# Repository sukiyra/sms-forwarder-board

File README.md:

# SMS Forwarder Board

面向 ESP32-C3 与 ML307 系列蜂窝模组的短信网关固件、Web 管理台和 Windows 批量量产工具。

这是由 [sukiyra](https://github.com/sukiyra) 独立维护和发布的工程仓库，GitHub 仓库本身不是 Fork。固件、管理台、设备自检协议、版本发布和量产流程在同一个仓库维护。

## 主要能力

- 自动识别 ML307A、ML307C、ML307R、ML307Y，并按模组能力选择短信上报方式。
- 国内版 ML307C 可在移动、联通、电信网络注册；本产品的短信收发只承诺中国移动和中国联通，电信网络仍可用于数据连接但界面会明确标记短信不可用。
- 支持实体 SIM 与 eSIM/eUICC；白卡初始化错误会自动容错，首页分别显示卡识别、短信配置和蜂窝注册状态。
- 接收和主动发送短信；短信使用固定 50 条循环存储，不会无限占用 Flash。
- 支持企业微信、飞书、Bark、电子邮件、钉钉、PushPlus、Server 酱、Gotify、Telegram 及自定义 HTTP 推送。
- 可扫描运营商、严格手动选网和恢复自动选网；目标网络拒绝时自动恢复可用网络。
- 初始化引导自动扫描附近 Wi-Fi，可选择网络、输入密码并在保存前测试连接；系统设置中也可随时更换主备网络。
- Wi-Fi 断线时自动保活并轮询主备网络；持续无法恢复会自动开启 `sms-forwarder` 热点进入手动配网。
- 人可读通知统一显示北京时间；开放 API 与本地记录继续使用 UTC ISO-8601，便于程序可靠解析和排序。
- 响应式 Web 管理台，适配手机、普通桌面和超宽屏；仪表盘并列显示蜂窝与 Wi-Fi 五级信号图，跨页面保留 OTA、选网、切卡和短信发送进度。
- 设备健康面板实时显示堆内存占用、启动以来最低余量、最大连续内存块、碎片率、LittleFS 占用、运行时间和上次复位原因；低内存、严重碎片或存储异常会标红。
- Windows 量产工具支持在线选择 GitHub Release 版本、多串口并行烧录和逐台验收。
- Windows 局域网发现工具可自动列出同网段设备，并一键打开对应管理页面。
- 支持从 GitHub Releases 在线检查和安装 OTA 更新；通过资产 API 绕过部分网络对 GitHub 下载页的连接限制，分段下载时持续回报字节数和进度，并使用双应用分区、HTTPS 证书校验、SHA-256 校验与启动失败自动回滚。
- 每台设备输出 CSV 与 JSON 量产记录，不记录短信正文、Wi-Fi 密码或推送密钥。

## 下载与烧录

打开仓库的 [Releases](https://github.com/sukiyra/sms-forwarder-board/releases)，每个版本提供三个压缩包和一个 OTA 固件：

- `sms-forwarder-firmware-vX.Y.Z.zip`：带 SHA-256 清单的 ESP32-C3 固件。
- `sms-forwarder-production-tool-windows-vX.Y.Z.zip`：Windows 单文件量产工具与 `esptool.exe`。
- `sms-forwarder-lan-scanner-windows-vX.Y.Z.zip`：自动发现局域网设备并打开管理台。
- `sms-forwarder-ota-vX.Y.Z.bin`：设备在线升级使用的应用镜像。

普通用户只需下载 Windows 工具包并解压：

1. 双击 `sms-forwarder-production-tool.exe`。
2. 在“GitHub 版本”中选择要烧录的版本。
3. 插入一块或多块设备，点击“刷新串口”。
4. 选择设备后开始烧录。
5. 只把显示 `PASS` 的设备作为通过品。

在线固件会缓存在 `%LOCALAPPDATA%\SMS Forwarder Production Tool\firmware`。工具会验证 Release 压缩包结构、清单版本和每个镜像的 SHA-256；断网时可以切换到本地固件目录。

## 局域网设备发现

升级到 v1.6.0 或更高版本后，解压并运行 `sms-forwarder-lan-scanner.exe`。工具会扫描电脑的 IPv4 局域网，列出设备 IP、固件版本、模组型号、OTA 能力、MAC 和设备 ID；双击设备即可打开管理台。

发现协议使用 UDP 37888 和每次扫描生成的随机 nonce。设备只回应同一子网请求，并限制回复频率。报文不包含手机号、ICCID、短信、Wi-Fi 密码、登录密码或推送密钥。路由器开启 AP 隔离或访客网络隔离时，设备之间无法互相发现。

## 支持的硬件

| 部件 | 要求 |
| --- | --- |
| 主控 | ESP32-C3，4 MB Flash |
| 开发板配置 | MakerGO ESP32 C3 SuperMini |
| 蜂窝模组 | ML307A / ML307C / ML307R / ML307Y AT 固件 |
| 串口 | ESP32 GPIO3 → ML307 RX；GPIO4 ← ML307 TX |
| 模组使能 | ESP32 GPIO5 → ML307 EN |
| 供电 | 需满足模组发射瞬时电流，主控与模组共地 |

不同 ML307 完整料号支持的频段和运营商不同。固件能够适配 AT 指令差异，但不能为硬件增加缺失的射频频段。采购和量产前必须按完整丝印、模组规格书、SIM 套餐及当地网络实测。

## 首次启动

设备没有可用 Wi-Fi 配置时会开启 `sms-forwarder` 配置热点。连接后访问 `http://192.168.4.1`，初始化引导会自动扫描附近网络；选择 Wi-Fi、输入密码并完成连接测试后保存。设备接入局域网后，通过路由器分配的 IP 打开管理台。

运行期间断线时，设备先使用 ESP32 自动重连保活。持续 2 分钟仍未恢复会按顺序非阻塞尝试最多 5 个已保存网络，每个网络最多等待 12 秒；全部失败后自动恢复 `sms-forwarder` 配置热点。此时重新连接热点即可修改 Wi-Fi，不需要清空其他系统配置。

默认管理员账号为 `admin`，初始密码为 `admin123`。首次登录后请立即在“系统设置”中修改密码。管理页面使用局域网 HTTP，不应直接映射到公网。

## 手动编译

需要 Arduino CLI、ESP32 Arduino Core 3.3.11，以及以下库：

- `pdulib@0.5.11`
- `ReadyMail@0.4.2`
- `ArduinoJson@7.4.2`

PowerShell：

```powershell
arduino-cli compile `
  --fqbn esp32:esp32:makergo_c3_supermini `
  --build-property upload.maximum_size=1966080 `
  --output-dir .\build `
  .\code
```

仓库内的 `code/partitions.csv` 定义 4 MB Flash 双应用分区：`app0` 与 `app1` 各 1,920 KB，并保留 NVS、OTA 状态、128 KB LittleFS 短信存储和 64 KB 崩溃转储分区。不要用 Arduino 菜单中的单应用分区覆盖它。

## 短信通知内容

v1.6.6 起，企业微信、Bark、钉钉、飞书、PushPlus、Server酱、Gotify、Telegram 和邮件共用完整的接收信息。通知会带上发送方、接收卡内号码、SIM / Profile、运营商与 PLMN、ICCID 尾号、设备名称与 ID、模组型号和北京时间；分段不完整时也会注明。号码读取失败会显示“SIM 未提供”，不会用管理员号码代替。

```text
短信转发 · 收到新短信
发送者：+8613800138000
接收号码：+8613900139000（卡内号码，未验证）
接收卡：WEBBING · eSIM / eUICC
运营商：中国联通 [46001]
ICCID：尾号 7707
设备：SMS FWD · ML307A · DEMO00000001
时间：2026-10-25 14:20:02（北京时间）

内容：
收到的短信原文
```

卡内号码来自 `AT+CNUM`，可能为空、过期或与实际业务号码不符，请以发卡方资料为准。通知页可查看当前设备的格式样例，配置回显默认隐藏密钥；“保存并测试”会先保存当前表单，再向目标通道发送测试消息。

标准 POST JSON 保留原有 `sender`、`message`、`timestamp` 字段，并添加接收卡与设备信息；GET 同样保留原参数并添加元数据。自定义 JSON 模板支持以下字符串变量，替换时自动进行 JSON 转义：

| 变量 | 内容 |
| --- | --- |
| `{sender}` / `{message}` / `{timestamp}` | 发送方、原始正文、原始时间 |
| `{receiver}` / `{profile}` / `{sim_type}` | 卡内号码、接收 Profile、卡类型 |
| `{carrier}` / `{plmn}` / `{iccid_tail}` | 运营商、驻网编号、ICCID 尾号 |
| `{device}` / `{device_id}` / `{model}` | 设备名称、设备 ID、模组 |
| `{display_time}` / `{notification}` | 北京时间、完整通知正文 |

例如 `{"text":"{notification}"}`。短信原文中恰好包含的变量文本会原样保留，不会被再次替换。企业微信仍按 UTF-8 字节拆分长消息，每段都会附上接收信息并遵守 2048 字节上限。

## 在线 OTA

在“系统设置 → 在线固件升级”中检查并安装正式版。设备只接受本仓库最新 GitHub Release 中名称为 `sms-forwarder-ota-vX.Y.Z.bin` 的资产，并验证以下条件：

- HTTPS 证书链有效，设备时间已通过 NTP 同步。
- 目标版本高于当前版本，不允许在线降级。
- 文件名称、Content-Length、Release 资产大小和备用分区容量一致。
- 下载完成后的 SHA-256 与 GitHub Release 资产摘要一致。
- ESP32 镜像头和写入完整性通过 Update/bootloader 校验。

固件始终写入非活动分区。下载中断、摘要不符或写入失败不会切换启动分区；新版本首次启动必须完成配置、WiFi、Web 服务和模组初始化，之后才会确认镜像。此前发生崩溃或看门狗复位时，bootloader 会回滚到旧版本。

短信记录固定为 50 条循环存储，系统日志固定为 80 条且每条最多 320 字节，运营商扫描、长短信和任务队列也使用固定容量。管理台的健康面板会保留 ESP32 自启动以来的最低空闲堆指标，用于发现缓慢泄漏；量产和长期运行仍应使用实际电源、SIM 与网络做持续老化测试。

从旧分区升级时，必须先用当前量产包通过 USB 完整烧录一次分区表。只写入应用 BIN 或从已装在旧分区上的 v1.6.3 在线升级，都会保留旧分区表，无法创建 LittleFS；管理台会明确显示“分区需迁移”。完成这次迁移后，后续版本可直接在线升级。需要保留现有配置时，在量产工具中关闭“全片擦除”；NVS 地址保持不变。

## 量产工具命令行

```powershell
# 查询 GitHub 可烧录版本
python .\factory\production_tool.py --list-versions

# 选择指定 Release，并烧录所有自动识别的 ESP32 串口
python .\factory\production_tool.py --all --version v1.6.0 --require-sim --require-network

# 使用最新 Release，保留设备已有配置
python .\factory\production_tool.py --ports COM3 --version latest --keep-data

# 只运行工厂自检
python .\factory\production_tool.py --ports COM3 --skip-flash --require-sim --require-network
```

更多操作见 [量产工具说明](factory/README.md)。协议与模块结构见 [开发文档](dev_doc/README.md)。

## 发布流程

推送 `v*` 标签会自动执行：

1. Python 与 C++ 测试。
2. 嵌入式 JavaScript 语法检查。
3. ESP32-C3 固件编译。
4. 固件清单、USB 烧录 ZIP 与 OTA 应用镜像打包。
5. Windows 单文件量产工具和局域网发现工具构建。
6. 创建 GitHub Release 并上传固件包、OTA 镜像、量产工具和局域网发现工具。

## 许可证与来源

固件、Web 管理台和量产工具使用 [MIT License](LICENSE)。新仓库由 sukiyra 独立维护；早期 MIT 代码的版权声明和来源记录保存在 [NOTICE](NOTICE) 中。提交修复和功能前请确保不包含 SIM 完整 ICCID、手机号、Wi-Fi 密码或推送密钥。

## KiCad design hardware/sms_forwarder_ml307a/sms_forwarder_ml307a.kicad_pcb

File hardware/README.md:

# SMS Forwarder Board Rev 1.0

这是与本仓库固件配套的 USB 棒形短信转发硬件。主控为 ESP32-C3-MINI-1，蜂窝模组为 ML307A-DSLN；ML307A-DCLN 可作为不需要 GNSS 时的替代料。工程使用 KiCad 10 创建，制造文件按立创/JLCPCB 四层板工艺导出。

Rev 1.0 是等待首板验证的工程样板。KiCad 10.0.6 ERC 与 DRC 均为 0 错误、0 警告、0 未连接，但这不能替代实体板的电源瞬态、射频、热、SMT 焊接和运营商网络测试。建议先下单 5 块裸板、贴装 2 块，完成 [装配与验证步骤](ASSEMBLY.md) 后再量产。

## 主要特性

- 40 mm × 84 mm 四层 PCB，USB-A 直插供电与原生 USB 下载。
- ESP32-C3 GPIO3/GPIO4 通过 TXU0202 与 ML307 的 1.8 V UART0 相连。
- ESP32-C3 GPIO5 控制 SY8205 的 EN，实现固件需要的模组硬断电重启。
- ML307 独立 3.816 V 同步降压电源，模组旁配置 2 × 220 µF 低 ESR 储能电容。
- Nano SIM 卡座、四路 SIM ESD、22 Ω 串联阻尼及 DATA 上拉。
- LTE MAIN 与可选 GNSS 两个 U.FL 接口，均预留 π 型匹配位。
- RESET、BOOT 按键和量产测试点。

## 文件目录

| 文件 | 用途 |
| --- | --- |
| `sms_forwarder_ml307a/` | KiCad 10 原理图、PCB、工程文件和 Specctra DSN |
| `libs/` | 项目专用符号、封装与 3D 模型 |
| `manufacturing/SMS-Forwarder-ML307A-Gerber.zip` | 可上传到立创下单页的 Gerber/钻孔压缩包 |
| `manufacturing/bom/BOM_JLCPCB.csv` | 立创 SMT BOM |
| `manufacturing/bom/BOM_Full.csv` | 含 DNP、手焊件与测试焊盘的完整 BOM |
| `manufacturing/bom/SMS-Forwarder-BOM.xlsx` | 便于采购、替代料和备注管理的 BOM |
| `manufacturing/pick-and-place/CPL_JLCPCB.csv` | JLC 标准列名的双面贴片坐标 |
| `drawings/schematic.pdf` | 原理图 PDF |
| `drawings/pcb-layout.pdf` | PCB 顶层装配图 |
| `tools/generate_hardware.py` | 重新生成器件布局、网表、DSN 与 BOM |

## 模组兼容性

本 PCB Rev 1.0 的焊盘仅适用于 **ML307A 94-pin 封装**。ML307C 与 ML307Y 使用 109-pin LCC+LGA 封装，虽然固件能够在运行时识别 A/C/Y 并选择兼容 AT 指令，但它们不能直接焊到本版 ML307A 焊盘上。C/Y 需要单独的 109-pin PCB 变体，不能通过软件解决封装差异。

这一区分也适用于量产：在贴片订单里必须把 `ML307A-DSLN / C5375091` 或 `ML307A-DCLN / C5362285` 与 PCB 版本绑定，不能让工厂按库存替换成 ML307C/Y。

## 立创下单参数

- 板层：4 层
- 板厚：1.6 mm
- 外层铜厚：1 oz
- 内层铜厚：0.5 oz
- 推荐叠层：JLC04161H-7628
- 阻抗：LTE/GNSS 走线按 50 Ω 单端复核；USB D+/D− 按 90 Ω 差分复核
- 表面处理：沉金 1U" 或无铅喷锡
- 阻焊/丝印：绿色/白色
- 最小信号线宽/间距：0.20/0.18 mm；局部接地扇出 0.15 mm
- 最小过孔：0.60/0.30 mm；模组电源过孔 1.00/0.50 mm
- 拼板：首轮不要拼板，先做 5 片工程样板

下单时选择与工程一致的阻抗叠层，并在阻抗计算器中重新确认最终线宽。立创可能调整材料批次或阻抗补偿，制造端给出的补偿值优先于工程中的名义线宽。

`BOM_JLCPCB.csv` 和 `CPL_JLCPCB.csv` 可直接用于 SMT 询价。USB-A 插头 J1 标为手焊件，RF 匹配电容 C23–C26 标为 DNP，测试点不会出现在贴片坐标中。立创导入后仍要逐项核对器件方向，特别是 U1、U2、J2、D1、D2、U3、U5、U6 和 U7。

## 供电要求

ML307 在 LTE 发射时会产生接近 2 A 的峰值电流。USB 电源必须能持续提供 5 V/2 A，并使用低阻 USB 接口或短延长线。普通电脑 USB 2.0 端口可能限流，表现为模组掉线、收不到短信、来电提示关机或反复注册。

板上 2 A 自恢复保险用于故障保护，不代表任意电脑 USB 端口都能提供 2 A。调试时应在 `TP1/+5V` 和 `TP2/+3V8_MODEM` 测量最低电压；模组发射期间 3.8 V 电源不能跌破 3.4 V。

## 首板验证

首批仅贴装 2 片，按 [装配与验证步骤](ASSEMBLY.md)逐项验收。通过电源纹波、UART、电流峰值、SIM、三网驻网、收发短信、Wi-Fi 和 24 小时压力测试后，再放开批量贴片。

## 重新生成

安装 KiCad 10 后运行 `hardware/tools/generate_hardware.py` 可重新生成放置完成的 PCB、DSN 和 CSV BOM。使用 Freerouting 1.6.5 对 DSN 布线后，以 `hardware/tools/import_freerouting.py` 导回 KiCad，再运行 `hardware/tools/generate_schematic.py` 和 KiCad CLI 导出制造资料。仓库内提交的 `.kicad_pcb` 已包含最终布线，不需要为了下单重新运行生成脚本。

## 许可证

`hardware/` 下的硬件源文件与制造资料使用 [CERN-OHL-P-2.0](LICENSE-CERN-OHL-P-2.0.txt)。仓库其余固件和量产工具继续使用根目录 MIT License。

## 设计依据

- [Espressif ESP32-C3 硬件设计指南](https://documentation.espressif.com/esp-hardware-design-guidelines/en/latest/esp32c3/index.html)
- [ESP32-C3-MINI-1/-1U 数据手册](https://documentation.espressif.com/esp32-c3-mini-1_datasheet_en.html)
- [JLCPCB 四层阻抗叠层](https://jlcpcb.com/impedance)
- ML307A Hardware Design Manual V1.0.1（仓库不再分发供应商手册；请从模组供应商取得当前版本）

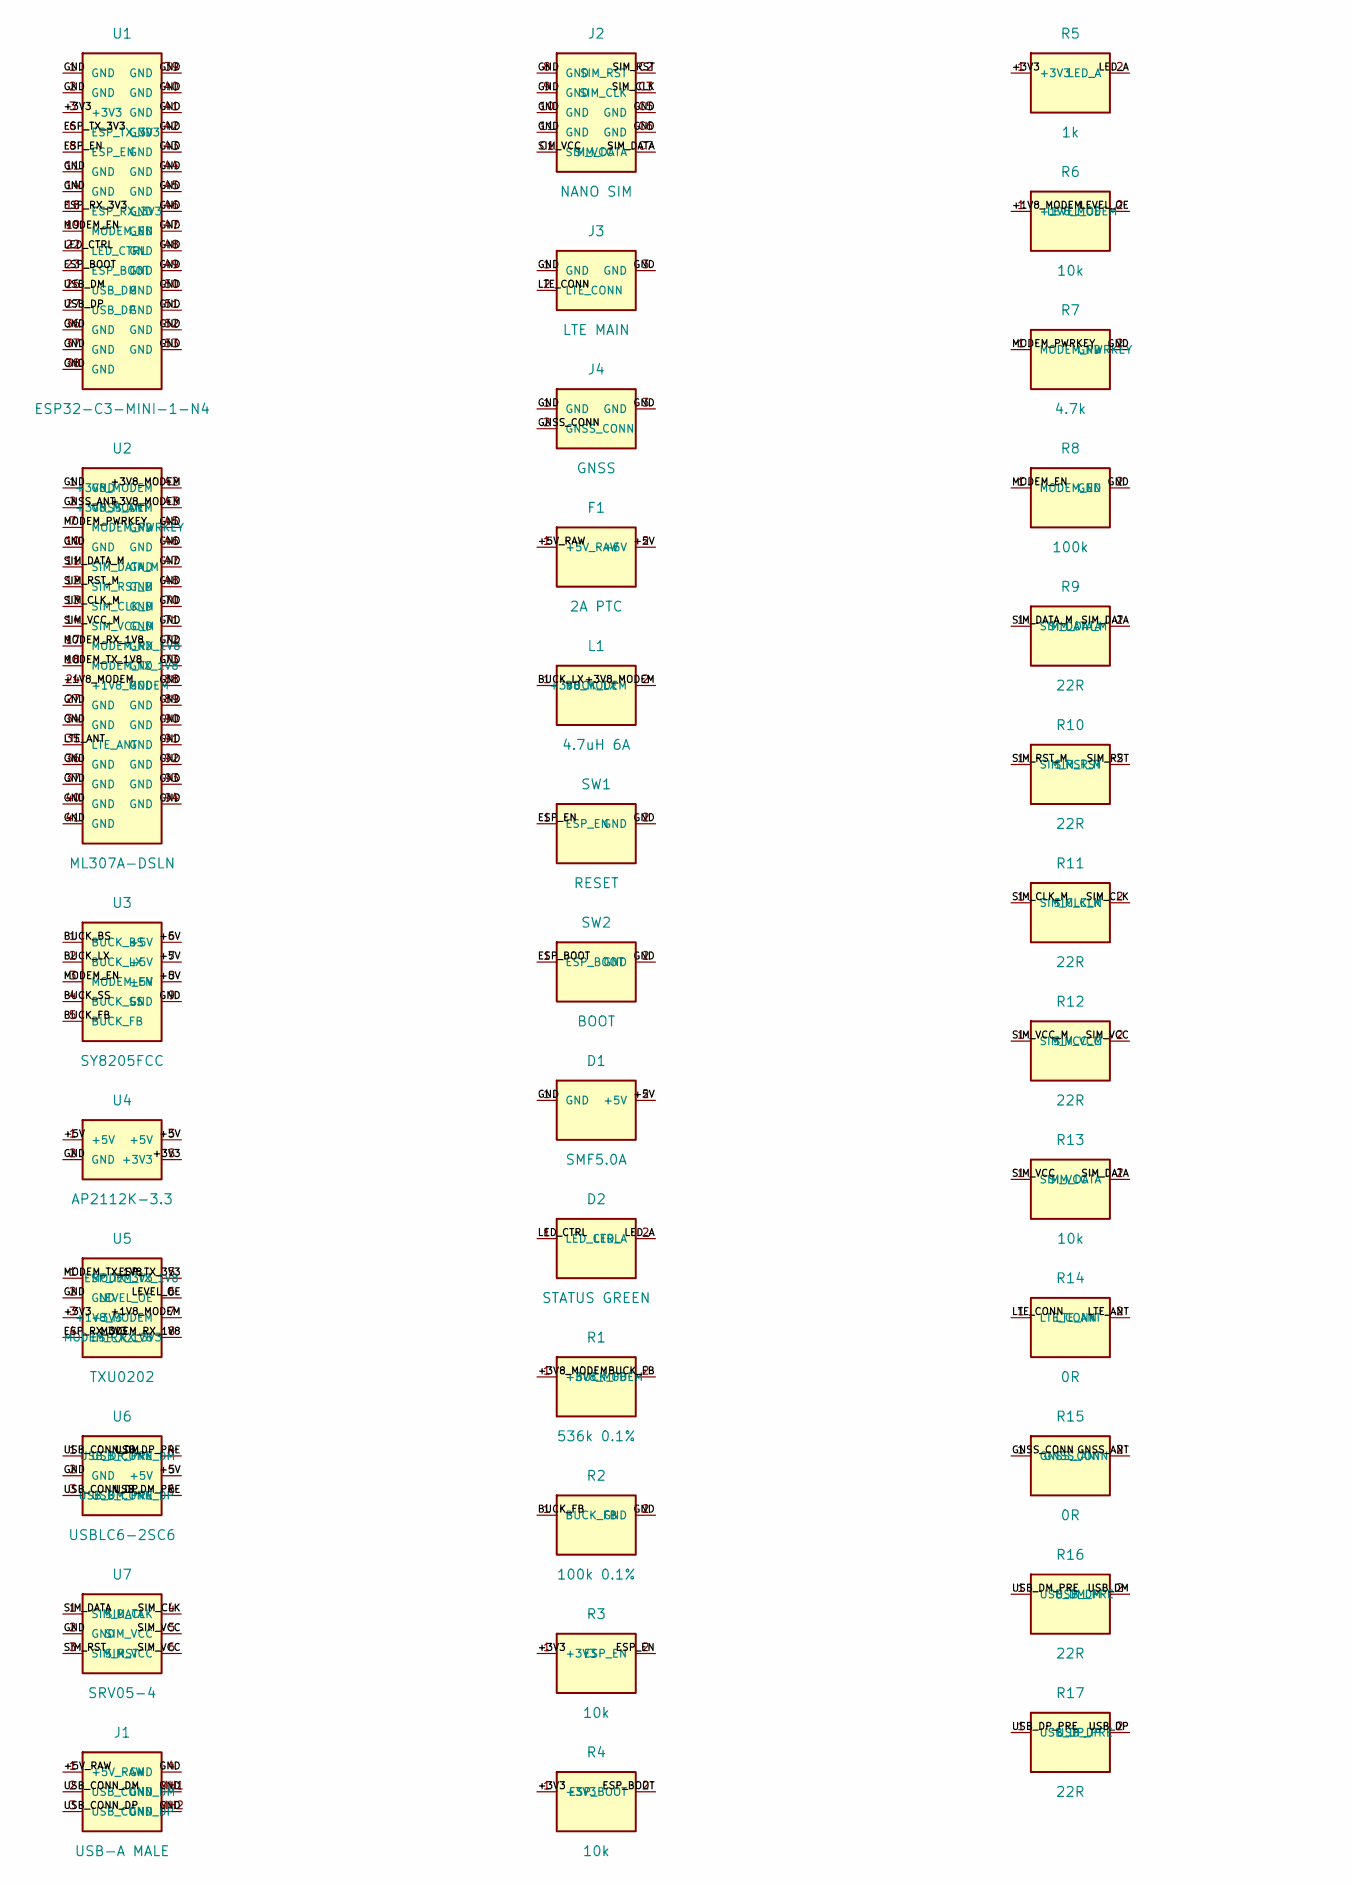
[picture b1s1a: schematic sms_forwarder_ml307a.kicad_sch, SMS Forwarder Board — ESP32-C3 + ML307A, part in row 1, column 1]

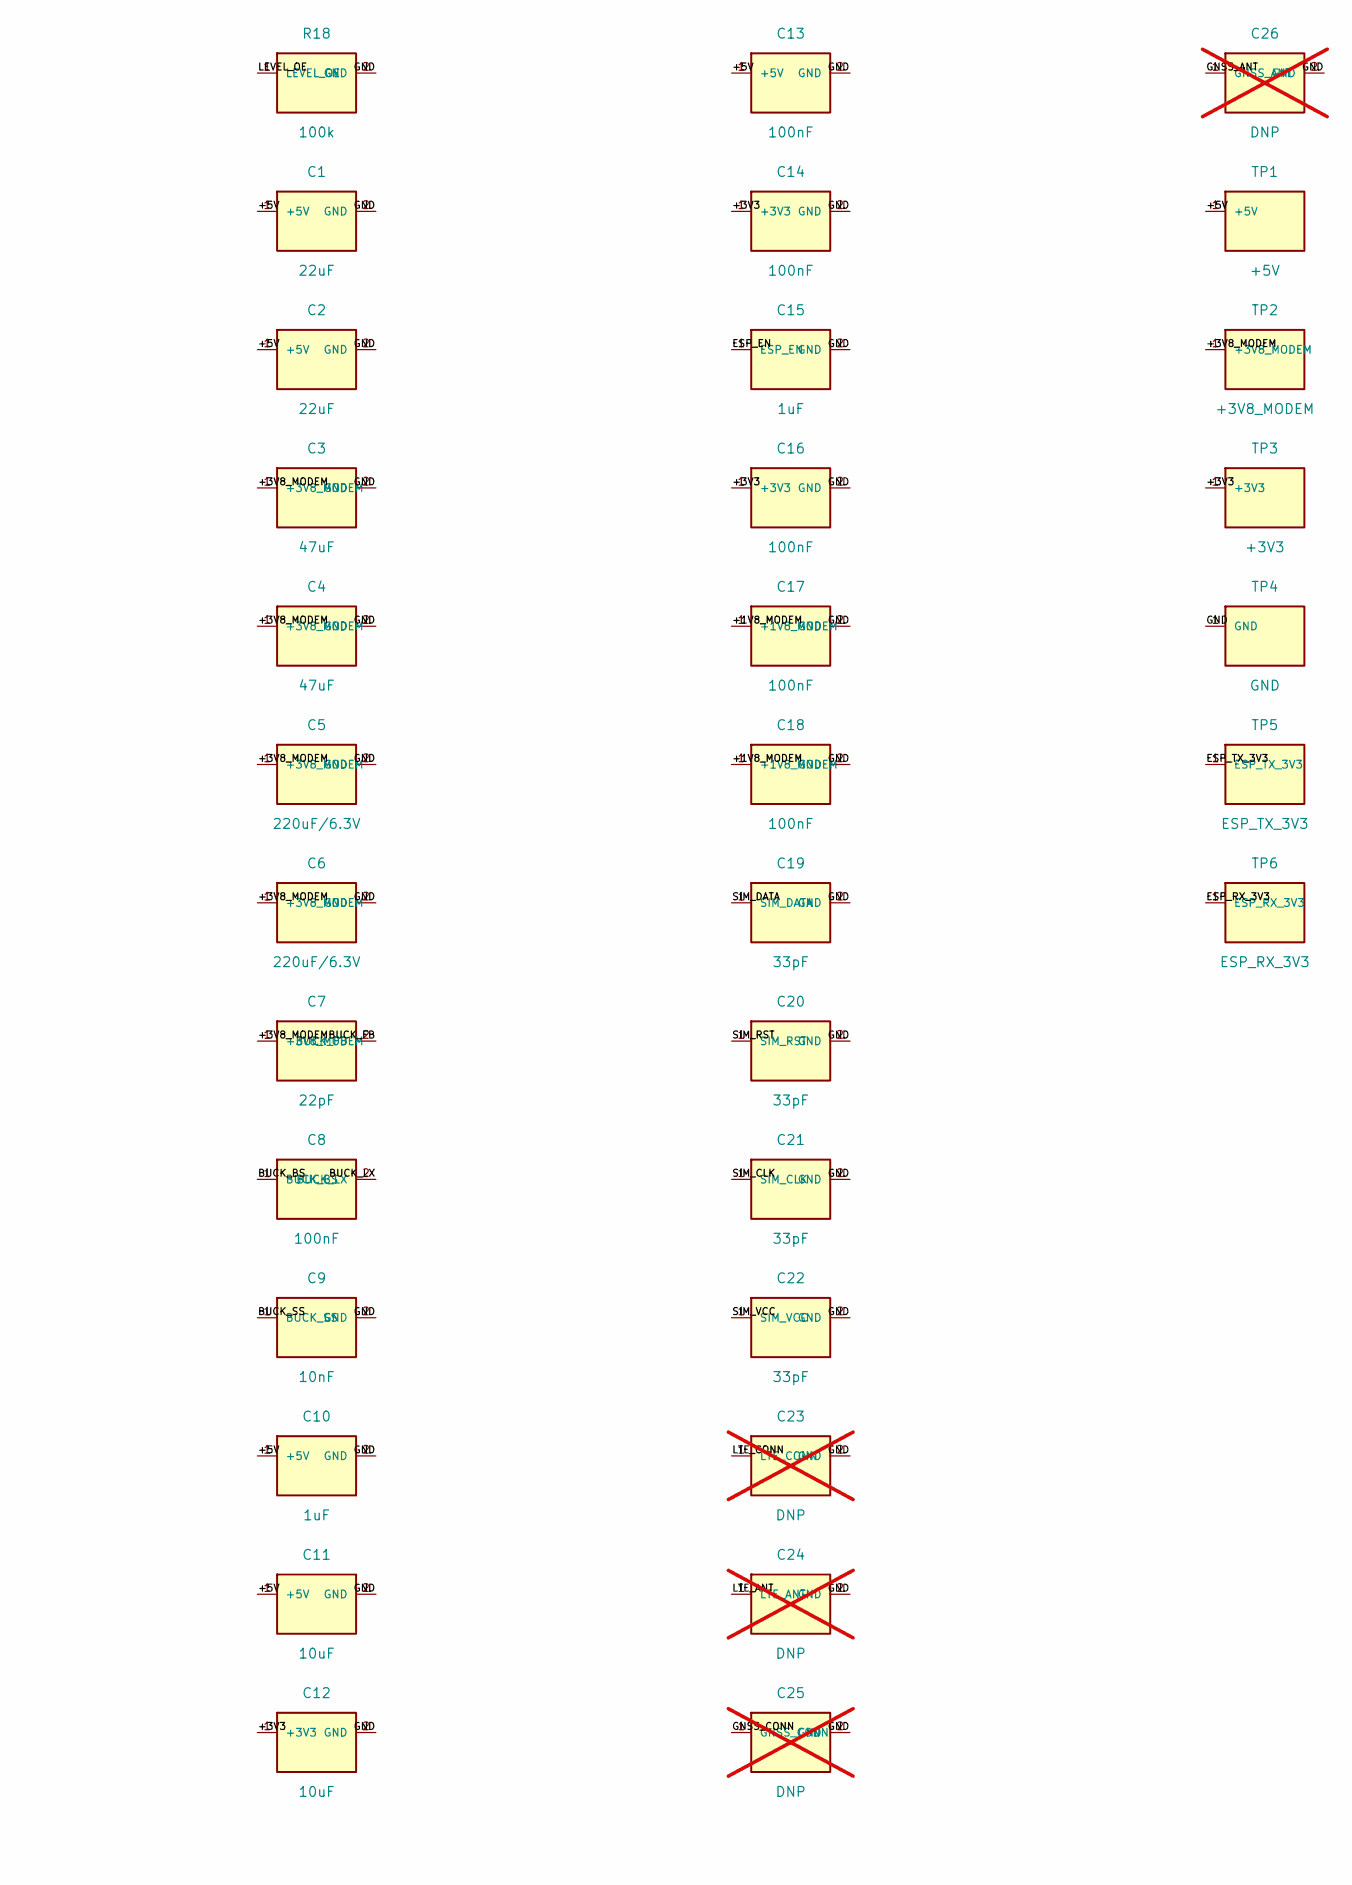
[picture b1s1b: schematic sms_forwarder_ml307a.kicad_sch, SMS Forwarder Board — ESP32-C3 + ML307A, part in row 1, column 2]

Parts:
C1, C2: 22uF; C_0805_2012Metric
C3, C4: 47uF; C_0805_2012Metric
C5, C6: 220uF/6.3V; CAP-SMD_BD5.0-L5.3-W5.3-LS5.7-FD
C7: 22pF; C_0402_1005Metric
C8, C13, C14, C16, C17, C18: 100nF; C_0402_1005Metric
C9: 10nF; C_0402_1005Metric
C10, C15: 1uF; C_0402_1005Metric
C11, C12: 10uF; C_0603_1608Metric
C19, C20, C21, C22: 33pF; C_0402_1005Metric
C23, C24, C25, C26: DNP; C_0402_1005Metric; not fitted
D1: SMF5.0A; D_SOD-123F
D2: STATUS GREEN; LED_0603_1608Metric
F1: 2A PTC; F1206
J1: USB-A MALE; USB-AM-TH_AM90
J2: NANO SIM; SIM-SMD_NANO-SIM-6PIN-1.45H
J3: LTE MAIN; ANT-SMD_UFL-R-SMT-1-10
J4: GNSS; ANT-SMD_UFL-R-SMT-1-10
L1: 4.7uH 6A; IND-SMD_L7.0-W6.6
R1: 536k 0.1%; R_0402_1005Metric
R2: 100k 0.1%; R_0402_1005Metric
R3, R4, R6, R13: 10k; R_0402_1005Metric
R5: 1k; R_0402_1005Metric
R7: 4.7k; R_0402_1005Metric
R8, R18: 100k; R_0402_1005Metric
R9, R10, R11, R12, R16, R17: 22R; R_0402_1005Metric
R14, R15: 0R; R_0402_1005Metric
SW1: RESET; SW_Tactile_SPST_NO_Straight_CK_PTS636Sx25SMTRLFS
SW2: BOOT; SW_Tactile_SPST_NO_Straight_CK_PTS636Sx25SMTRLFS
TP1: +5V; TestPoint_Pad_D1.0mm
TP2: +3V8_MODEM; TestPoint_Pad_D1.0mm
TP3: +3V3; TestPoint_Pad_D1.0mm
TP4: GND; TestPoint_Pad_D1.0mm
TP5: ESP_TX_3V3; TestPoint_Pad_D1.0mm
TP6: ESP_RX_3V3; TestPoint_Pad_D1.0mm
U1: ESP32-C3-MINI-1-N4; WIFIM-SMD_ESP32-C3-MINI-1
U2: ML307A-DSLN; LGA-94_L17.7-W15.8_N706-CA-01-S1
U3: SY8205FCC; SOIC-8_L5.0-W4.0-P1.27-LS6.0-BL-EP2.0
U4: AP2112K-3.3; SOT-25-5_L2.9-W1.6-P0.95-LS2.8-BL
U5: TXU0202; VSSOP-8_L2.3-W2.0-P0.50-LS3.1-BR
U6: USBLC6-2SC6; SOT-23-6_L2.9-W1.6-P0.95-LS2.8-BL
U7: SRV05-4; SOT-23-6_L2.9-W1.6-P0.95-LS2.8-BL

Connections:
+1V8_MODEM: C17.1 (+1V8_MODEM), C18.1 (+1V8_MODEM), R6.1 (+1V8_MODEM), U2.24 (+1V8_MODEM), U5.7 (+1V8_MODEM)
+3V3: C12.1 (+3V3), C14.1 (+3V3), C16.1 (+3V3), R3.1 (+3V3), R4.1 (+3V3), R5.1 (+3V3), TP3.1, U1.3 (+3V3), U4.5 (+3V3), U5.3 (+3V3)
+3V8_MODEM: C3.1 (+3V8_MODEM), C4.1 (+3V8_MODEM), C5.1 (+3V8_MODEM), C6.1 (+3V8_MODEM), C7.1 (+3V8_MODEM), L1.2 (+3V8_MODEM), R1.1 (+3V8_MODEM), TP2.1, U2.42 (+3V8_MODEM), U2.43 (+3V8_MODEM)
+5V: C1.1 (+5V), C2.1 (+5V), C10.1 (+5V), C11.1 (+5V), C13.1 (+5V), D1.2 (+5V), F1.2 (+5V), TP1.1, U3.6 (+5V), U3.7 (+5V), U3.8 (+5V), U4.1 (+5V), U4.3 (+5V), U6.5 (+5V)
+5V_RAW: F1.1 (+5V_RAW), J1.1 (+5V_RAW)
BUCK_BS: C8.1 (BUCK_BS), U3.1 (BUCK_BS)
BUCK_FB: C7.2 (BUCK_FB), R1.2 (BUCK_FB), R2.1 (BUCK_FB), U3.5 (BUCK_FB)
BUCK_LX: C8.2 (BUCK_LX), L1.1 (BUCK_LX), U3.2 (BUCK_LX)
BUCK_SS: C9.1 (BUCK_SS), U3.4 (BUCK_SS)
ESP_BOOT: R4.2 (ESP_BOOT), SW2.1 (ESP_BOOT), U1.23 (ESP_BOOT)
ESP_EN: C15.1 (ESP_EN), R3.2 (ESP_EN), SW1.1 (ESP_EN), U1.8 (ESP_EN)
ESP_RX_3V3: TP6.1, U1.18 (ESP_RX_3V3), U5.4 (ESP_RX_3V3)
ESP_TX_3V3: TP5.1, U1.6 (ESP_TX_3V3), U5.5 (ESP_TX_3V3)
GND: C1.2 (GND), C2.2 (GND), C3.2 (GND), C4.2 (GND), C5.2 (GND), C6.2 (GND), C9.2 (GND), C10.2 (GND), C11.2 (GND), C12.2 (GND), C13.2 (GND), C14.2 (GND), C15.2 (GND), C16.2 (GND), C17.2 (GND), C18.2 (GND), C19.2 (GND), C20.2 (GND), C21.2 (GND), C22.2 (GND), C23.2 (GND), C24.2 (GND), C25.2 (GND), C26.2 (GND), D1.1 (GND), J1.4 (GND), J1.MH1 (GND), J1.MH2 (GND), J2.8 (GND), J2.9 (GND), J2.10 (GND), J2.11 (GND), J2.C5 (GND), J2.C6 (GND), J3.1 (GND), J3.3 (GND), J4.1 (GND), J4.3 (GND), R2.2 (GND), R7.2 (GND), R8.2 (GND), R18.2 (GND), SW1.2 (GND), SW2.2 (GND), TP4.1, U1.1 (GND), U1.2 (GND), U1.11 (GND), U1.14 (GND), U1.36 (GND), U1.37 (GND), U1.38 (GND), U1.39 (GND), U1.40 (GND), U1.41 (GND), U1.42 (GND), U1.43 (GND), U1.44 (GND), U1.45 (GND), U1.46 (GND), U1.47 (GND), U1.48 (GND), U1.49 (GND), U1.50 (GND), U1.51 (GND), U1.52 (GND), U1.53 (GND), U2.1 (GND), U2.10 (GND), U2.27 (GND), U2.34 (GND), U2.36 (GND), U2.37 (GND), U2.40 (GND), U2.41 (GND), U2.45 (GND), U2.46 (GND), U2.47 (GND), U2.48 (GND), U2.70 (GND), U2.71 (GND), U2.72 (GND), U2.73 (GND), U2.88 (GND), U2.89 (GND), U2.90 (GND), U2.91 (GND), U2.92 (GND), U2.93 (GND), U2.94 (GND), U3.9 (GND), U4.2 (GND), U5.2 (GND), U6.2 (GND), U7.2 (GND)
GNSS_ANT: C26.1 (GNSS_ANT), R15.2 (GNSS_ANT), U2.2 (GNSS_ANT)
GNSS_CONN: C25.1 (GNSS_CONN), J4.2 (GNSS_CONN), R15.1 (GNSS_CONN)
LED_A: D2.2 (LED_A), R5.2 (LED_A)
LED_CTRL: D2.1 (LED_CTRL), U1.22 (LED_CTRL)
LEVEL_OE: R6.2 (LEVEL_OE), R18.1 (LEVEL_OE), U5.6 (LEVEL_OE)
LTE_ANT: C24.1 (LTE_ANT), R14.2 (LTE_ANT), U2.35 (LTE_ANT)
LTE_CONN: C23.1 (LTE_CONN), J3.2 (LTE_CONN), R14.1 (LTE_CONN)
MODEM_EN: R8.1 (MODEM_EN), U1.19 (MODEM_EN), U3.3 (MODEM_EN)
MODEM_PWRKEY: R7.1 (MODEM_PWRKEY), U2.7 (MODEM_PWRKEY)
MODEM_RX_1V8: U2.17 (MODEM_RX_1V8), U5.8 (MODEM_RX_1V8)
MODEM_TX_1V8: U2.18 (MODEM_TX_1V8), U5.1 (MODEM_TX_1V8)
SIM_CLK: C21.1 (SIM_CLK), J2.C3 (SIM_CLK), R11.2 (SIM_CLK), U7.4 (SIM_CLK)
SIM_CLK_M: R11.1 (SIM_CLK_M), U2.13 (SIM_CLK_M)
SIM_DATA: C19.1 (SIM_DATA), J2.C7 (SIM_DATA), R9.2 (SIM_DATA), R13.2 (SIM_DATA), U7.1 (SIM_DATA)
SIM_DATA_M: R9.1 (SIM_DATA_M), U2.11 (SIM_DATA_M)
SIM_RST: C20.1 (SIM_RST), J2.C2 (SIM_RST), R10.2 (SIM_RST), U7.3 (SIM_RST)
SIM_RST_M: R10.1 (SIM_RST_M), U2.12 (SIM_RST_M)
SIM_VCC: C22.1 (SIM_VCC), J2.C1 (SIM_VCC), R12.2 (SIM_VCC), R13.1 (SIM_VCC), U7.5 (SIM_VCC), U7.6 (SIM_VCC)
SIM_VCC_M: R12.1 (SIM_VCC_M), U2.14 (SIM_VCC_M)
USB_CONN_DM: J1.2 (USB_CONN_DM), U6.1 (USB_CONN_DM)
USB_CONN_DP: J1.3 (USB_CONN_DP), U6.3 (USB_CONN_DP)
USB_DM: R16.2 (USB_DM), U1.26 (USB_DM)
USB_DM_PRE: R16.1 (USB_DM_PRE), U6.6 (USB_DM_PRE)
USB_DP: R17.2 (USB_DP), U1.27 (USB_DP)
USB_DP_PRE: R17.1 (USB_DP_PRE), U6.4 (USB_DP_PRE)

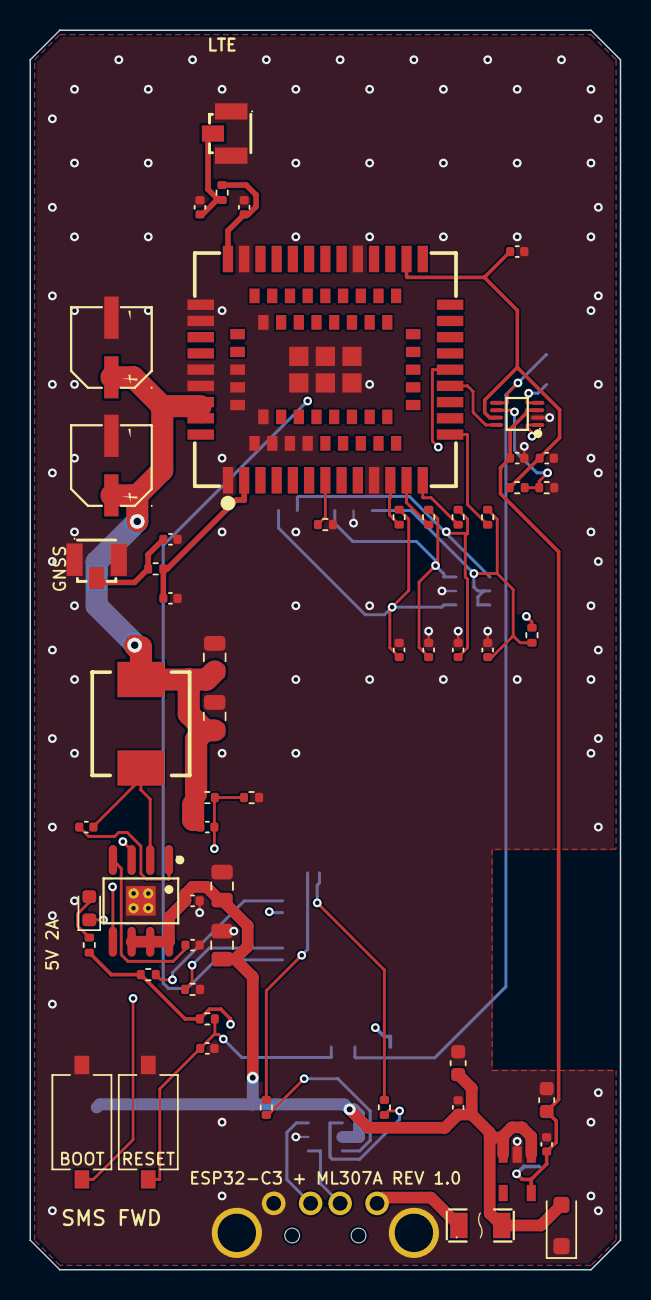
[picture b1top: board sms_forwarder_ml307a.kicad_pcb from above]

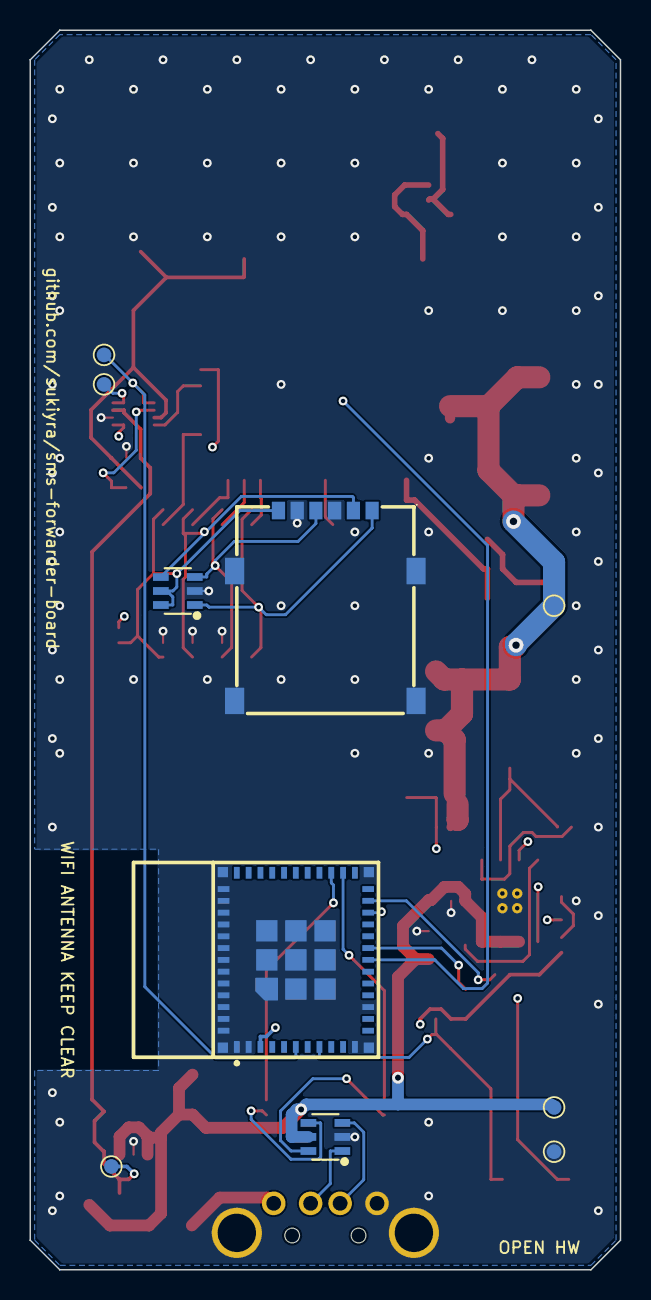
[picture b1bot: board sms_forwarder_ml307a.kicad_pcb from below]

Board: 4 copper layers, 40.0 x 84.0 mm, 67 parts (10 on the bottom side), 39 nets.

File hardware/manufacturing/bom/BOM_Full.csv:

Comment,Designator,Footprint,LCSC Part #,Quantity,Manufacturer,Manufacturer Part #,Assembly,Notes
ESP32-C3-MINI-1-N4,U1,SMD 13.2x16.6 mm,C2838502,1,Espressif,ESP32-C3-MINI-1-N4,SMT,
ML307A-DSLN,U2,LGA-94 17.7x15.8 mm,C5375091,1,China Mobile IoT,ML307A-DSLN,SMT,Alternative: ML307A-DCLN / C5362285. Do not fit ML307C/Y on this PCB revision.
SY8205FCC,U3,SOIC-8-EP,C111875,1,Silergy,SY8205FCC,SMT,
AP2112K-3.3,U4,SOT-23-5,C51118,1,Diodes Incorporated,AP2112K-3.3TRG1,SMT,
TXU0202,U5,VSSOP-8,C5186957,1,Texas Instruments,TXU0202DCUR,SMT,
USBLC6-2SC6,U6,SOT-23-6,C2687116,1,UMW,USBLC6-2SC6,SMT,
SRV05-4,U7,SOT-23-6,C558418,1,TECH PUBLIC,SRV05-4,SMT,
USB-A male,J1,THT,C404965,1,Korean Hroparts Elec,AM90,THT/manual,
Nano SIM,J2,SMD 1.45 mm,C53200251,1,XYECONN,NANO SIM 6PIN 1.45H,SMT,
U.FL,"J3,J4",SMD,C88373,2,Hirose,U.FL-R-SMT-1(10),SMT,
2 A PTC,F1,1206,C70167,1,TECHFUSE,SL1206200,SMT,
4.7 uH,L1,7.0x6.6 mm,C5307631,1,XR,XR0630-4R7M,SMT,
220 uF 6.3 V,"C5,C6",D5xL5.3 mm,C2162607,2,Nippon Chemi-Con,APXF6R3ARA221ME61G,SMT,
22 uF 10 V,"C1,C2",0805,C45783,2,Samsung,CL21A226MPQNNNE,SMT,
47 uF 6.3 V,"C3,C4",0805,C96123,2,Samsung,CL21A476MQYNNNE,SMT,
10 uF 10 V,"C11,C12",0603,C19702,2,Samsung,CL10A106KP8NNNC,SMT,
100 nF,"C8,C13,C14,C16,C17,C18",0402,C1525,6,Samsung,CL05B104KO5NNNC,SMT,
10 nF,C9,0402,C15195,1,Samsung,CL05B103KB5NNNC,SMT,
1 uF,C10,0402,C52923,1,Samsung,CL05A105KA5NNNC,SMT,
1 uF,C15,0402,C52923,1,Samsung,CL05A105KA5NNNC,SMT,
22 pF,C7,0402,C1555,1,Samsung,CL05C220JB5NNNC,SMT,
33 pF,"C19,C20,C21,C22",0402,C1562,4,Samsung,CL05C330JB5NNNC,SMT,
DNP,"C23,C24,C25,C26",0402,,4,-,DNP,DNP,Select after antenna/VNA validation.
536 k,R1,0402,C72998,1,UNI-ROYAL,0402WGF5363TCE,SMT,
100 k,R2,0402,C25741,1,UNI-ROYAL,0402WGF1003TCE,SMT,
10 k,"R3,R4,R6,R13",0402,C25744,4,UNI-ROYAL,0402WGF1002TCE,SMT,
4.7 k,R7,0402,C25900,1,UNI-ROYAL,0402WGF4701TCE,SMT,
100 k,"R8,R18",0402,C25741,2,UNI-ROYAL,0402WGF1003TCE,SMT,
22 R,"R9,R10,R11,R12,R16,R17",0402,C25092,6,UNI-ROYAL,0402WGF220JTCE,SMT,
0 R,"R14,R15",0402,C17168,2,UNI-ROYAL,0402WGF0000TCE,SMT,
1 k,R5,0402,C11702,1,UNI-ROYAL,0402WGF1001TCE,SMT,
SMF5.0A,D1,SOD-123FL,C1509112,1,JSCJ,SMF5.0A,SMT,
Green LED,D2,0603,C965804,1,XINGLIGHT,XL-1608UGC-04,SMT,
Tact switch,"SW1,SW2",3.0x2.5 mm SMD,C72443,2,C&K,KMR221GLFS,SMT,
Test pad,"TP1,TP2,TP3,TP4,TP5,TP6",1.0 mm pad,,6,-,PCB pad,PCB,

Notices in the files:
hardware/sms_forwarder_ml307a/sms_forwarder_ml307a.kicad_sch:
CERN-OHL-P-2.0 open hardware
